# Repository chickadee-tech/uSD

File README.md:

# Chickadee Tech MicroSD Polystack Mod #
This mod adds a microSD card to a Polystack.

## Documentation ##
See the [wiki](https://github.com/chickadee-tech/uSD/wiki) for documentation.

## Polystack ##
This **mod** board is part of the Polystack platform for modular microcontrol systems. More information on the platform can be found at [polystack.org](http://polystack.org).

## Support ##
If you need support with a board you own or have development questions please email support@chickadee.tech or check [chickadee.tech/support](https://chickadee.tech/support) for other ways to get support.

## Contributing ##
Please note that this project is released with a [Contributor Code of Conduct](CODE_OF_CONDUCT.md). By participating in this project you agree to abide by its terms.

### Setup ###
Components and footprints for PCB parts are not included in this repository. Instead, checkout the [chickadee-tech/kicad-libs](https://github.com/chickadee-tech/kicad-libs) repository in the same directory that this repository is checked out in. All part definitions should be relative so that they will load correctly.

### Pull requests ###
For fixes please submit a pull request to the original repository. After the pull request is merged, check the [Chickadee Tech Active Contributor Discount (ACD)](https://chickadee.tech/active-contributor) to see if you are eligible for a discount code to use on your next purchase.

### Derivatives ###
If developing your own version of the MicroSD board please remove all Chickadee Tech trademarks and follow the [CC-BY license](LICENSE). While not required, please consider open sourcing your modifications so others can learn from your improvements. If you do email support@chickadee.tech and we may choose to add your project to the ACD.

You may also license the Polystack logo for free by emailing support@chickadee.tech. We'll ask for your gerbers to ensure the design complies with specifications laid out [here](https://github.com/chickadee-tech/polystack/wiki) and provide written permission to use the trademark after compliance has been demonstrated.

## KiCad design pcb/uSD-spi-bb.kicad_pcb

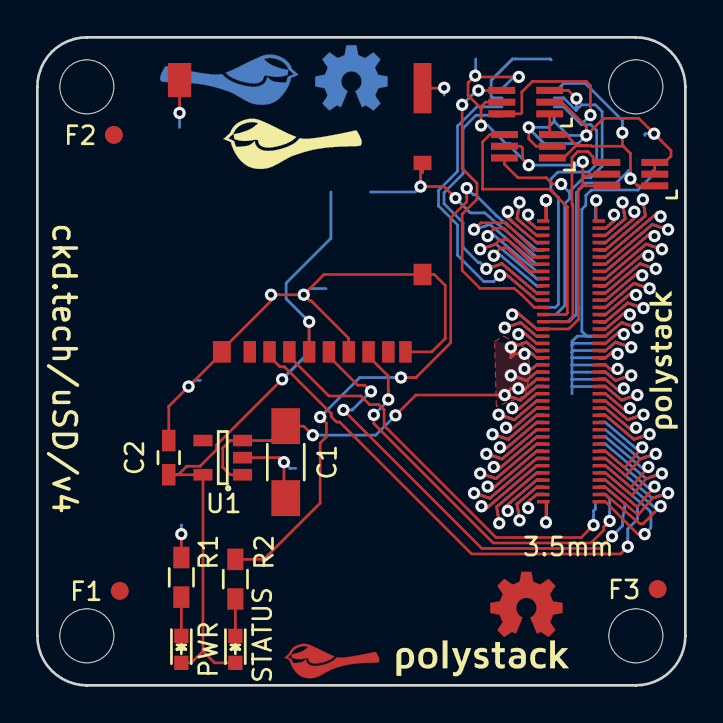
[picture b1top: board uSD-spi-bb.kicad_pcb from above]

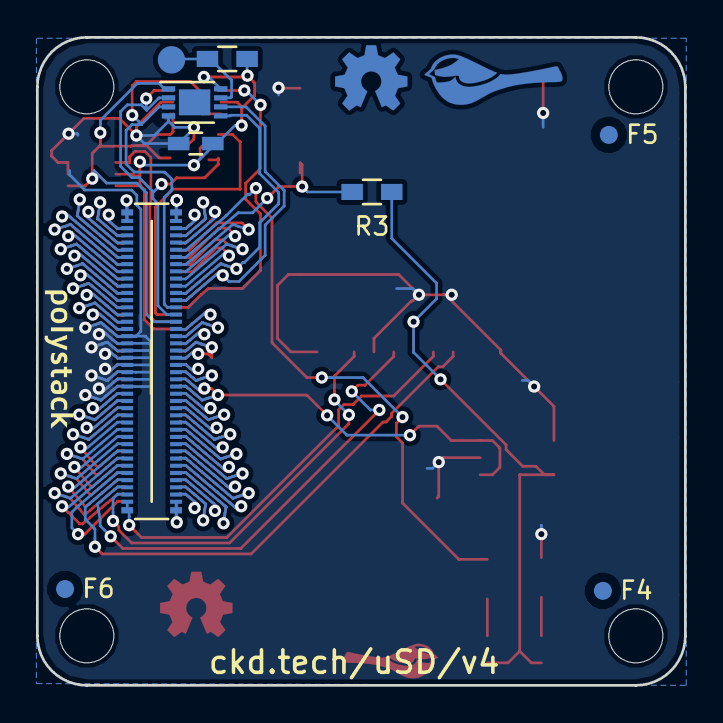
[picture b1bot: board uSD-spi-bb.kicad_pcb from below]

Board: 2 copper layers, 36.0 x 36.0 mm, 27 parts (10 on the bottom side), 75 nets.

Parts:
C1: 10uF; C_1206_HandSoldering
C2: 1uF; C_0603_HandSoldering
D1: RED; LED_0603
D2: GREEN; LED_0603
F1, F2, F3, F4, F5, F6: 1mm; Fiducial
PORT_ANDOR1: SN74LVC1G0832; SC-70-6_Handsoldering
PORT_C1: 0.1uF; C_0603_HandSoldering
PORT_IC1: AT24CS02-MAHM; DFN-8-1EP_3x2mm_Pitch0.5mm
PORT_IN1: CKD_SANDWICH; DF40-80pin-Header
PORT_INV1: SN74LVC1G58; SC-70-6_Handsoldering
PORT_OUT1: CKD_SANDWICH; DF40-3-4mm-80pin-Receptacle
PORT_P1: CONN_01X01; Measurement_Point_Round-SMD-Pad_Small
PORT_R1: 10k; R_0603_HandSoldering
PORT_XOR1: SN74LVC1G58; SC-70-6_Handsoldering
R1, R2: 1k; R_0603_HandSoldering
R3: 10k; R_0603_HandSoldering
U1: TLV70233DBV; SOT-23-5
U2: MicroSD; DM3AT
svg2mod: G***; polystack-bold-0.5
svg2mod#2, svg2mod#3: G***; polystack-bold-0.4

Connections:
+3V3: C2.1, D1.2, D2.2, R3.1, U1.5, U2.4
+5V: C1.1, PORT_IN1.19, PORT_IN1.20, PORT_IN1.21, PORT_IN1.22, PORT_IN1.23, PORT_IN1.24, PORT_OUT1.19, PORT_OUT1.20, PORT_OUT1.21, PORT_OUT1.22, PORT_OUT1.23, PORT_OUT1.24, U1.1, U1.3
/ExpansionPort/3V3_0.3A_E: PORT_IN1.17, PORT_OUT1.17
/ExpansionPort/3V3_0.3A_LL: PORT_ANDOR1.5, PORT_C1.1, PORT_IC1.8, PORT_IN1.16, PORT_INV1.5, PORT_INV1.6, PORT_OUT1.16, PORT_R1.2, PORT_XOR1.5
/ExpansionPort/+BATT: PORT_IN1.18, PORT_OUT1.18
/ExpansionPort/ADC1: PORT_IN1.49, PORT_OUT1.49
/ExpansionPort/ADC2: PORT_IN1.50, PORT_OUT1.50
/ExpansionPort/BOOT: PORT_IN1.65, PORT_OUT1.65
/ExpansionPort/CAN_HI: PORT_IN1.67, PORT_OUT1.67
/ExpansionPort/CAN_LO: PORT_IN1.68, PORT_OUT1.68
/ExpansionPort/GPIO1: PORT_IN1.5, R2.2
/ExpansionPort/GPIO2: PORT_IN1.6, R3.2, U2.14
/ExpansionPort/GPIO3: PORT_IN1.7, PORT_OUT1.5
/ExpansionPort/GPIO4: PORT_IN1.8, PORT_OUT1.6
/ExpansionPort/GPIO5: PORT_IN1.9, PORT_OUT1.7
/ExpansionPort/GPIO6: PORT_IN1.10, PORT_OUT1.8
/ExpansionPort/HEIGHT_1: PORT_ANDOR1.1, PORT_IC1.1, PORT_IN1.15, PORT_INV1.1, PORT_XOR1.1, PORT_XOR1.3
/ExpansionPort/HEIGHT_2: PORT_ANDOR1.3, PORT_IC1.2, PORT_IN1.14, PORT_XOR1.6
/ExpansionPort/HEIGHT_4: PORT_ANDOR1.6, PORT_IC1.3, PORT_IN1.13
/ExpansionPort/NEW_HEIGHT_1: PORT_INV1.4, PORT_OUT1.15
/ExpansionPort/NEW_HEIGHT_2: PORT_OUT1.14, PORT_XOR1.4
/ExpansionPort/NEW_HEIGHT_4: PORT_ANDOR1.4, PORT_OUT1.13
/ExpansionPort/RESET: PORT_IN1.66, PORT_OUT1.66
/ExpansionPort/SDMMC1_CK: PORT_IN1.55, PORT_OUT1.55
/ExpansionPort/SDMMC1_CMD: PORT_IN1.56, PORT_OUT1.56
/ExpansionPort/SDMMC1_D0: PORT_IN1.51, PORT_OUT1.51
/ExpansionPort/SDMMC1_D1: PORT_IN1.52, PORT_OUT1.52
/ExpansionPort/SDMMC1_D2: PORT_IN1.53, PORT_OUT1.53
/ExpansionPort/SDMMC1_D3: PORT_IN1.54, PORT_OUT1.54
/ExpansionPort/SPI1_MISO: PORT_IN1.79, U2.7
/ExpansionPort/SPI1_MOSI: PORT_IN1.80, U2.3
/ExpansionPort/SPI1_NSS: PORT_IN1.77, U2.2
/ExpansionPort/SPI1_SCK: PORT_IN1.78, U2.5
/ExpansionPort/SPI2_MISO: PORT_IN1.75, PORT_OUT1.79
/ExpansionPort/SPI2_MOSI: PORT_IN1.76, PORT_OUT1.80
/ExpansionPort/SPI2_NSS: PORT_IN1.73, PORT_OUT1.77
/ExpansionPort/SPI2_SCK: PORT_IN1.74, PORT_OUT1.78
/ExpansionPort/SPI3_MISO: PORT_IN1.71, PORT_OUT1.75
/ExpansionPort/SPI3_MOSI: PORT_IN1.72, PORT_OUT1.76
/ExpansionPort/SPI3_NSS: PORT_IN1.69, PORT_OUT1.73
/ExpansionPort/SPI3_SCK: PORT_IN1.70, PORT_OUT1.74
/ExpansionPort/TIM1: PORT_IN1.1, PORT_OUT1.1
/ExpansionPort/TIM2: PORT_IN1.2, PORT_OUT1.2
/ExpansionPort/TIM3: PORT_IN1.3, PORT_OUT1.3
/ExpansionPort/TIM4: PORT_IN1.4, PORT_OUT1.4
/ExpansionPort/TIMG1_CH1: PORT_IN1.41, PORT_OUT1.41
/ExpansionPort/TIMG1_CH2: PORT_IN1.42, PORT_OUT1.42
/ExpansionPort/TIMG1_CH3: PORT_IN1.43, PORT_OUT1.43
/ExpansionPort/TIMG1_CH4: PORT_IN1.44, PORT_OUT1.44
/ExpansionPort/TIMG2_CH1: PORT_IN1.45, PORT_OUT1.45
/ExpansionPort/TIMG2_CH2: PORT_IN1.46, PORT_OUT1.46
/ExpansionPort/TIMG2_CH3: PORT_IN1.47, PORT_OUT1.47
/ExpansionPort/TIMG2_CH4: PORT_IN1.48, PORT_OUT1.48
/ExpansionPort/UART1_RX: PORT_IN1.40, PORT_OUT1.40
/ExpansionPort/UART1_TX: PORT_IN1.39, PORT_OUT1.39
/ExpansionPort/UART2_RX: PORT_IN1.38, PORT_OUT1.38
/ExpansionPort/UART2_TX: PORT_IN1.37, PORT_OUT1.37
/ExpansionPort/UART3_RX: PORT_IN1.36, PORT_OUT1.36
/ExpansionPort/UART3_TX: PORT_IN1.35, PORT_OUT1.35
/ExpansionPort/UART4_RX: PORT_IN1.34, PORT_OUT1.34
/ExpansionPort/UART4_TX: PORT_IN1.33, PORT_OUT1.33
/ExpansionPort/UART5_RX: PORT_IN1.32, PORT_OUT1.32
/ExpansionPort/UART5_TX: PORT_IN1.31, PORT_OUT1.31
/ExpansionPort/UART6_RX: PORT_IN1.30, PORT_OUT1.30
/ExpansionPort/UART6_TX: PORT_IN1.29, PORT_OUT1.29
/ExpansionPort/UART7_RX: PORT_IN1.28, PORT_OUT1.28
/ExpansionPort/UART7_TX: PORT_IN1.27, PORT_OUT1.27
/ExpansionPort/UART8_RX: PORT_IN1.26, PORT_OUT1.26
/ExpansionPort/UART8_TX: PORT_IN1.25, PORT_OUT1.25
/ExpansionPort/i2c_SCL: PORT_IC1.6, PORT_IN1.12, PORT_OUT1.12
/ExpansionPort/i2c_SDA: PORT_IC1.5, PORT_IN1.11, PORT_OUT1.11
GNDPWR: C1.2, C2.2, PORT_ANDOR1.2, PORT_C1.2, PORT_IC1.4, PORT_IN1.57, PORT_IN1.58, PORT_IN1.59, PORT_IN1.60, PORT_IN1.61, PORT_IN1.62, PORT_IN1.63, PORT_IN1.64, PORT_INV1.2, PORT_INV1.3, PORT_OUT1.57, PORT_OUT1.58, PORT_OUT1.59, PORT_OUT1.60, PORT_OUT1.61, PORT_OUT1.62, PORT_OUT1.63, PORT_OUT1.64, PORT_XOR1.2, R1.2, U1.2, U2.6, U2.9, U2.10, U2.11, U2.12, U2.13
unnamed: D1.1, R1.1
unnamed: D2.1, R2.1
unnamed: PORT_IC1.7, PORT_P1.1, PORT_R1.1

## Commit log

2016-01-26 BlackBox logger that writes directly to a microSD card over SPI.
2016-04-07 Add card detect to uSD BB.
2016-04-11 Correct schematic label and save PDF of schematic for easy reference.
2016-04-13 Rebrand everything to Polystack and increment versions.
2016-04-16 Final gerbers for test manufacturing run.
2016-06-07 Update polystack logo to bold variant, remove 'bb' from url and bump version number.
2016-07-07 Add license information to many files. PCB design files are CC-BY and code is MIT license.
2016-07-07 Add back .gitignore after repo split.
2016-07-07 Convert to relative component and footprint paths.
2016-07-09 Switch to polystack lib.

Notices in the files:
pcb/uSD-spi-bb.kicad_pcb:
Copyright 2016 Chickadee Tech LLC,
This work is licensed under the Creative Commons Attribution 4.0 International License.
To view a copy of this license, visit http://creativecommons.org/licenses/by/4.0
or send a letter to Creative Commons, PO Box 1866, Mountain View, CA 94042, USA.
